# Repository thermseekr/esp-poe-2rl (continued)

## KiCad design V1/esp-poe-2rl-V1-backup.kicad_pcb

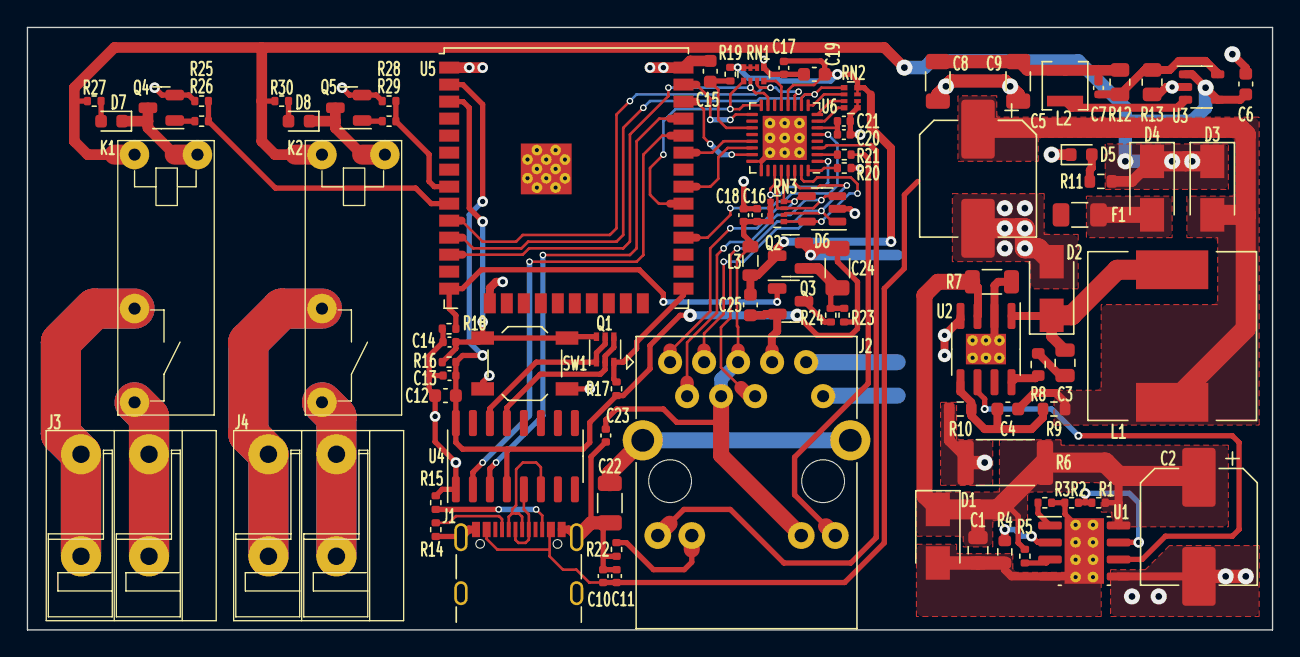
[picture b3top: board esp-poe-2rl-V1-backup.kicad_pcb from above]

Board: 2 copper layers, 93.0 x 45.0 mm, 88 parts (0 on the bottom side), 73 nets.

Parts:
C1, C3: 100nF/100V; C_0805_2012Metric
C2: 22uF/100V; CP_Elec_8x10.5
C4: 12pF/50V; C_0603_1608Metric
C5: 470uF/16V; CP_Elec_8x10.5
C6, C12, C15, C19, C25: 10uF/10V; C_0603_1608Metric
C7: 22pF/50V; C_0402_1005Metric
C8, C9, C24: 22uF/10V; C_1206_3216Metric
C10, C14, C20: 1uF/25V; C_0402_1005Metric
C11, C13, C16, C17, C18, C23: 0,1uF/50V; C_0402_1005Metric
C21: 470pF/50V; C_0402_1005Metric
C22: 1nF/2kV; C_1206_3216Metric
D1: SMAJ58A; D_SMA
D2: SS510; D_SMA
D3, D4: SS34; D_SMA
D5, D7, D8: GREEN; LED_0603_1608Metric
D6: ESDS314DBV; SOT-23-5
F1: 500mA; Fuse_1206_3216Metric
J1: USB_C_Receptacle_USB2.0; USB_C_Receptacle_GCT_USB4105-xx-A_16P_TopMnt_Horizontal
J2: RJ45 JACK; RJ45_UDE_RB1-ZZ-0206
J3, J4: 1x2P 5,08mm; TerminalBlock_Dibo_DB142R-2-5.08_1x02_P5.08mm_Horizontal
K1, K2: G5NB-1A-E-DC5; Relay_SPST_Omron_G5NB-1A
L1: 33uH/2,1A; L_12x12mm_h6mm
L2: 2,2uH/1,5A; L_3x3_h1.5
L3: 2A/600R; L_0805_2012Metric
Q1: UMH3N; SOT-363_SC-70-6
Q2: WPM2015-3/TR; SOT-23
Q3: LMUN2211LT1G; SOT-23
Q4, Q5: MMBT2222A; SOT-23
R1: 130k/62,5mW; R_0402_1005Metric
R2, R16, R17, R18, R19, R23, R25, R28: 10k/62,5mW; R_0402_1005Metric
R3: 180k/62,5mW; R_0402_1005Metric
R4: 4,42k/100mW; R_0603_1608Metric
R5: 30,1k/62,5mW; R_0402_1005Metric
R6: 4,7k/1W; R_2512_6332Metric
R7: 30mR/250mW; R_1206_3216Metric
R8: 5,1R/100mW; R_0603_1608Metric
R9: 300k/100mW; R_0603_1608Metric
R10: 52,3k/100mW; R_0603_1608Metric
R11: 820R/100mW; R_0603_1608Metric
R12: 100k/0,125W; R_0805_2012Metric
R13: 22,1k/0,125W; R_0805_2012Metric
R14, R15: 5,1k/62,5mW; R_0402_1005Metric
R20: 12,1k/62,5mW; R_0402_1005Metric
R21, R22: 330R/62,5mW; R_0402_1005Metric
R24, R26, R29: 1k/62,5mW; R_0402_1005Metric
R27, R30: 680R/62,5mW; R_0402_1005Metric
RN1, RN2: 4x2,2k/62,5mW; R_Array_Convex_4x0402
RN3: 4x49,9R/62,5mW; R_Array_Convex_4x0402
SW1: RESET; SW_SPST_TL3342
U1: TPS2376DDAR-H; SOIC-8-1EP_3.9x4.9mm_P1.27mm_EP2.95x4.9mm_Mask2.71x3.4mm_Th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
U2: TX4138; SOIC-8-1EP_3.9x4.9mm_P1.27mm_EP2.29x3mm_ThermalVias
U3: SY8089A1AAC; TSOT-23-5
U4: CH340C; SOIC-16_3.9x9.9mm_P1.27mm
U5: ESP32-WROOM-32UE-N16; ESP32-WROOM-32U
U6: LAN8710A; QFN-32-1EP_5x5mm_P0.5mm_EP3.3x3.3mm_ThermalVias

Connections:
5VPOE: C4.1, C5.1, D3.2 (A), L1.2, R9.1
5VUSB: D4.2 (A), F1.1
+3.3V: C7.1, C8.1, C9.1, C12.1, C13.1, C24.1, L2.2, Q2.2 (S), R12.1, R16.1, R17.1, R23.1, U4.4 (V3), U4.16 (VCC), U5.2 (VDD)
+3.3VA: C16.1, C18.1, C23.1, J2.4 (CT), J2.5 (CT), J2.12 (RLED+), L3.2, RN3.5 (R4.2), RN3.6 (R3.2), RN3.7 (R2.2), RN3.8 (R1.2), U6.1 (VDD2A), U6.27 (VDD1A)
+3.3VLAN: C17.1, C19.1, C25.1, L3.1, Q2.3 (D), R19.2, RN1.6 (R3.2), RN1.7 (R2.2), RN1.8 (R1.2), RN2.7 (R2.2), RN2.8 (R1.2), U6.12 (VDDIO)
+5V: C6.1, D3.1 (K), D4.1 (K), K1.1, K2.1, R11.1, R27.1, R30.1, U3.1 (EN), U3.4 (IN)
/EMAC_CLK: U5.28 (IO17), U6.5 (XTAL1/CLKIN)
/EMAC_MDC: U5.37 (IO23), U6.17 (MDC)
/EMAC_MDIO: RN1.1 (R1.1), U5.30 (IO18), U6.16 (MDIO)
/EMAC_RX: RN1.2 (R2.1), U5.12 (IO27), U6.15 (COL/CRS_DV/~MODE2)
/EMAC_RXD0: RN1.3 (R3.1), U5.10 (IO25), U6.11 (RXD0/~MODE0)
/EMAC_RXD1: RN2.1 (R1.1), U5.11 (IO26), U6.10 (RXD1/~MODE1)
/EMAC_TXD0: U5.31 (IO19), U6.22 (TXD0)
/EMAC_TXD1: U5.36 (IO22), U6.23 (TXD1)
/EMAC_TXEN: U5.33 (IO21), U6.21 (TXEN)
/LED_G_K: R21.2, U6.2 (LED2/~INTSEL)
/LED_Y_A: J2.14 (LLED+), U6.3 (LED1/~REGOFF)
/RD+: D6.5 (I/04), J2.3 (RD+), RN3.1 (R1.1), U6.31 (RXP)
/RD-: D6.1 (I/01), J2.6 (RD-), RN3.2 (R2.1), U6.30 (RXN)
/TD+: D6.4 (I/03), J2.1 (TD+), RN3.4 (R4.1), U6.29 (TXP)
/TD-: D6.3 (I/02), J2.2 (TD-), RN3.3 (R3.1), U6.28 (TXN)
/USB_D+: J1.A6 (D+), J1.B6 (D+), U4.5 (UD+)
/USB_D-: J1.A7 (D-), J1.B7 (D-), U4.6 (UD-)
GND: C2.2, C5.2, C6.2, C8.2, C9.2, C10.2, C11.2, C12.2, C13.2, C14.2, C15.1, C16.2, C17.2, C18.2, C19.2, C20.2, C21.2, C22.2, C23.2, C25.2, D2.2 (A), D5.1 (K), D6.2 (GND), J1.A1 (GND), J1.A12 (GND), J1.B1 (GND), J1.B12 (GND), J1.S1 (SHIELD), J2.7, Q3.2 (E), Q4.2 (E), Q5.2 (E), R6.2, R10.2, R13.2, R14.2, R15.2, R18.1, R20.2, R22.2, R25.2, R28.2, RN1.5 (R4.2), RN2.5 (R4.2), RN2.6 (R3.2), SW1.1, U1.5 (RTN), U2.4 (GND), U3.2 (GND), U4.1 (GND), U5.1 (GND), U5.15 (GND), U5.38 (GND), U5.39 (GND), U6.24 (TXD2), U6.25 (TXD3), U6.33 (VSS)
unnamed: C20.1, C21.1, U6.6 (VDDCR)
unnamed: C3.1, R8.1
unnamed: C10.1, C11.1, F1.2, J1.A4 (VBUS), J1.A9 (VBUS), J1.B4 (VBUS), J1.B9 (VBUS)
unnamed: C3.2, D2.1 (K), L1.1, U2.1 (SW)
unnamed: D5.2 (A), R11.2
unnamed: D7.2 (A), R27.2
unnamed: D7.1 (K), K1.4, Q4.3 (C)
unnamed: D8.2 (A), R30.2
unnamed: D8.1 (K), K2.4, Q5.3 (C)
unnamed: J1.A5 (CC1), R14.1
unnamed: J1.B5 (CC2), R15.1
unnamed: J2.13 (LLED-), R22.1
unnamed: J2.11 (RLED-), R21.1
unnamed: C22.1, J2.15 (SHIELD)
unnamed: J3.1, K1.2
unnamed: J3.2, K1.3
unnamed: J4.1, K2.2
unnamed: J4.2, K2.3
unnamed: Q1.2 (B1), Q1.4 (E2), U4.13 (~DTR)
unnamed: C14.1, Q1.6 (C1), R16.2, SW1.2, U5.3 (EN)
unnamed: Q1.1 (E1), Q1.5 (B2), U4.14 (~RTS)
unnamed: Q1.3 (C2), R17.2, U5.25 (IO0)
unnamed: C24.2, Q2.1 (G), R23.2, R24.1
unnamed: Q3.3 (C), R24.2
unnamed: Q4.1 (B), R26.1
unnamed: Q5.1 (B), R29.1
unnamed: R7.2, U2.2 (ILIM), U2.9 (ILIM)
unnamed: RN1.4 (R4.1), U6.13 (RXER/RXD4/~PHYAD0)
unnamed: RN2.2 (R2.1), U6.9 (RXD2/~RMIISEL)
unnamed: RN2.3 (R3.1), U6.8 (RXD3/~PHYAD2)
unnamed: RN2.4 (R4.1), U6.7 (RXCLK/~PHYAD1)
unnamed: R4.1, U1.2 (CLASS)
unnamed: R5.2, U1.3 (DET)
unnamed: R3.1, U1.1 (ILIM)
unnamed: R1.2, R2.1, U1.7 (UVLO)
unnamed: R8.2, U2.8 (BS)
unnamed: C4.2, R9.2, R10.1, U2.5 (FB)
unnamed: C7.2, R12.2, R13.1, U3.5 (FB)
unnamed: L2.1, U3.3 (LX)
unnamed: U4.3 (RXD), U5.35 (TXD0/IO1)
unnamed: U4.2 (TXD), U5.34 (RXD0/IO3)
unnamed: R20.1, U6.32 (RBIAS)
unnamed: C15.2, R19.1, U6.19 (~RST)
OUT1: R25.1, R26.2, U5.9 (IO33)
OUT2: R28.1, R29.2, U5.8 (IO32)
PG: U1.6 (PG), U2.6 (EN)
PHY_PWR: Q3.1 (B), R18.2, U5.14 (IO12)
PoE+: C1.1, C2.1, D1.1 (K), J2.9 (V+), R1.1, R5.1, R6.1, R7.1, U1.8 (VDD), U2.3 (VIN)
PoE-: C1.2, D1.2 (A), J2.10 (V-), R2.2, R3.2, R4.2, U1.4 (VSS), U1.9 (PPAD)

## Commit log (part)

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2023-08-02 First iteration
2023-08-07 Searching for the right connector...
2023-08-07 Backups
2023-08-08 Working on PoE frontend.
2023-08-08 Development
2023-08-09 Development continues!
2023-08-09 The dev saga goes on.
2023-08-10 Dev fest.
2023-08-11 Dev going on
2023-08-11 Dev dev dev
2023-08-12 dev goes on
2023-08-14 Topology ok, checking components values
2023-08-14 Revising components specs
2023-08-15 Reviewing components
2023-08-16 Starting layout
2023-08-16 Layout development
2023-08-16 Layouting
2023-08-17 Big layout
2023-08-17 PCB design
2023-08-18 Something, cant remember
2023-08-18 Squeezing layout
2023-08-18 Layout optimization
2023-08-18 Replace power connectors
2023-08-19 Connectors rotated 180deg
2023-08-21 Add these files to ignore list
2023-08-21 Repository reorg and cleanup
2023-08-24 Replaced relays
2023-08-25 Updating
2023-08-25 PCB shrinking process in course
2023-08-26 PCB shrinking process
2023-08-27 Migrating layout to 4 layers
2023-08-27 PCB dev
2023-08-28 Last touches
2023-08-29 Production testing
2023-09-02 Design optimization
2023-09-04 Tweaks to components
2023-09-04 New board image
2023-09-05 Update image
2024-11-06 Update to Kicad V8
2024-11-25 Added temperature sensor
2024-11-27 Added temperature sensor.
2024-11-27 Reviewing board for fabrication
2024-11-29 Preparations for fabrication
2024-11-30 Selecting components at JLCPCB
2024-12-02 Adjustment for case
2024-12-02 Case
2024-12-02 Replaced RJ45 connector
2024-12-03 Adjusting for component shortages at JLCPCB
2024-12-03 Adjust for components shortage at JLCPCB
2024-12-04 DIN holder
2024-12-05 Connectors repositioned to better fit the case
2024-12-07 V1.2.0
2025-04-14 Prefab checks
2025-06-24 Redoing routing because was too crapy
2025-06-24 Redoing routing
2025-06-29 Routing redone
2025-06-29 Production output
2025-06-29 Files for release 1.3.0
2025-06-29 Added license
2025-07-09 Generated fabrication files
2025-07-09 Fabrication file generated
2025-07-14 Fabrication updates
2025-07-31 Update GPIO template info
2025-07-31 Corrected leds connections on RJ45 jack
2026-02-04 V1.4
2026-02-04 Rerouting
